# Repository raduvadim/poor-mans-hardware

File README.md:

poor-mans-hardware
==================

open source equipment for engineer's workbench.

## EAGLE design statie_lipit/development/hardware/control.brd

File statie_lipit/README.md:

Statie de lipit
=======================

Schema logica

+---------------+		+---------------+ 24Vcc	+---------------+	+---------------+
|		|     24Vca	|  Stabilizator	|======>|    Comanda	|	|     Letcon	|
|Transformator	| ============>	|  de tensiune	|	|   incalzire	|	+---------------+
|		|		|		|  /===>|		|==\	|    Element 	|
|---------------+		+---------------+  ||	+---------------+  \===>|   incalzire	|
					||	   ||				|		|
					||5Vcc	   ||				+---------------+
					\/	   ||				|     Senzor	|
+---------------+		+---------------+  ||	+---------------+   /===|  temperatura	|
|   Terminal	|      UART	| Microprocesor |===/	|   Convertor	|<==/	|		|
|    Serial	|==============>|    Atmega 8	| SPI/ V|  Temperatura	|	+---------------+
|		|		|		|<======| Tensiune/Biti |
+---------------+		+---------------+	+---------------+
				   ||	     /\	
				   ||	     ||
				   \/	     ||
			+---------------+    ||	+---------------+
			|     Afisaj    |    ||	|    Butoane/	|
			|  LCD/7segment |    \==|Encoder rotativ|
			| 		|	| /Potentiometru|
			+---------------+	+---------------+

Design modular
 -Circuitistica statiei de lipit este impartita in patru placi:
	-Alimentare si comanda incalzire
	-Microprocesor
	-Achizitie si conversie temperatura
	-Afisaj si input
 -Placile au dimensiunea de 2,4x1,5inch(6x3,8cm) si au 4 gauri de montare in colturi.

Model asezare placi:

	        +----------+     +     +     +     +
	       /	  /|====/|====/|====/|====/|
	      /		 / |   / |   / |   / |   / |
	     /		/  |  /	 |  /  |  /  |  /  |
	    /	       /   | /	 | /   | /   | /   |
	   /          /	   |/	 |/    |/    |/    | 
	  /	     /	   /	 /     /     /     +
	 /	    /	  /	/     /     /     /
	+----------+     +     +     +     +     /
	|	   |=====|=====|=====|=====|    /
	|	   |	/|    /|     |     |   /
	|   traf   |   / |   / |     |     |  /
	|	   |  /	 |  /  |     |     | /
	|	   |=====|=====|=====|=====|/ 
	+----------+     +     +     +     +
	
			 ^     ^     ^	   ^placa afisaj si butoane
			 |     |     placa microprocesor
		  	 |	placa achizitie temperatura	
			 placa stabilizare tensiune si control incalzire

Design frontal statie lipit:

	+----------------------------+
        |			     |
	| +---------------+	     |
	| |		  |   #####  |
	| |	LCD/	  |   #PWR#  |
	| |   7segmente	  |   #####  |
	| |		  |          |
	| +---------------+	     |
	|  /-\   /-\   /-\    #####  |
	|  \-/   \-/   \-/    #Con#  |
	|		      #####  |
        +----------------------------+

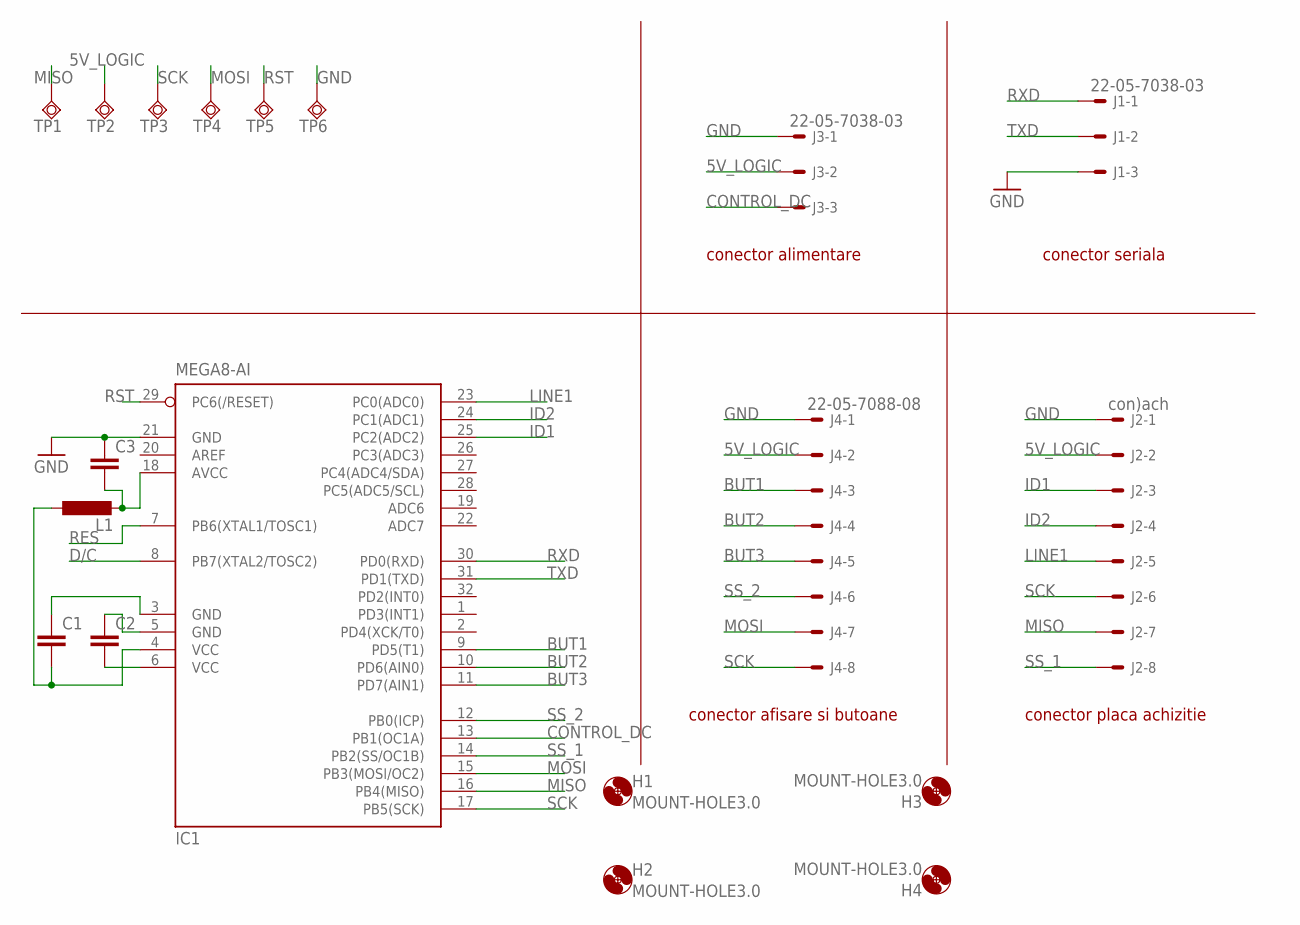
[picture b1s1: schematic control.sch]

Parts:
C1, C2, C3: C-EUC0805K; C0805K
H1, H2, H3, H4: MOUNT-HOLE3.0; 3,0
IC1: MEGA8-AI; TQFP32-08
J1, J3: 22-05-7038-03; 7395-03
J2: con)ach; 7395-08
J4: 22-05-7088-08; 7395-08
L1: L-EU0204/7; 0204/7
TP1, TP2, TP3, TP4, TP5, TP6: TPSQPAD1-13; P1-13

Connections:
5V_LOGIC: C1.2, C2.2, IC1.4 (VCC), IC1.6 (VCC), J2.2, J3.2, J4.2, L1.1, TP2.TP
BUT1: IC1.9 (PD5(T1)), J4.3
BUT2: IC1.10 (PD6(AIN0)), J4.4
BUT3: IC1.11 (PD7(AIN1)), J4.5
CONTROL_DC: IC1.13 (PB1(OC1A)), J3.3
D/C: IC1.8 (PB7(XTAL2/TOSC2))
GND: C1.1, C2.1, C3.1, IC1.3 (GND), IC1.5 (GND), IC1.21 (GND), J1.3, J2.1, J3.1, J4.1, TP6.TP
ID1: IC1.25 (PC2(ADC2)), J2.3
ID2: IC1.24 (PC1(ADC1)), J2.4
LINE1: IC1.23 (PC0(ADC0)), J2.5
MISO: IC1.16 (PB4(MISO)), J2.7, TP1.TP
MOSI: IC1.15 (PB3(MOSI/OC2)), J4.7, TP4.TP
unnamed: C3.2, IC1.18 (AVCC), L1.2
RES: IC1.7 (PB6(XTAL1/TOSC1))
RST: IC1.29 (PC6(/RESET)), TP5.TP
RXD: IC1.30 (PD0(RXD)), J1.1
SCK: IC1.17 (PB5(SCK)), J2.6, J4.8, TP3.TP
SS_1: IC1.14 (PB2(SS/OC1B)), J2.8
SS_2: IC1.12 (PB0(ICP)), J4.6
TXD: IC1.31 (PD1(TXD)), J1.2

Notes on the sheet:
conector seriala
conector placa achizitie
conector alimentare
conector afisare si butoane

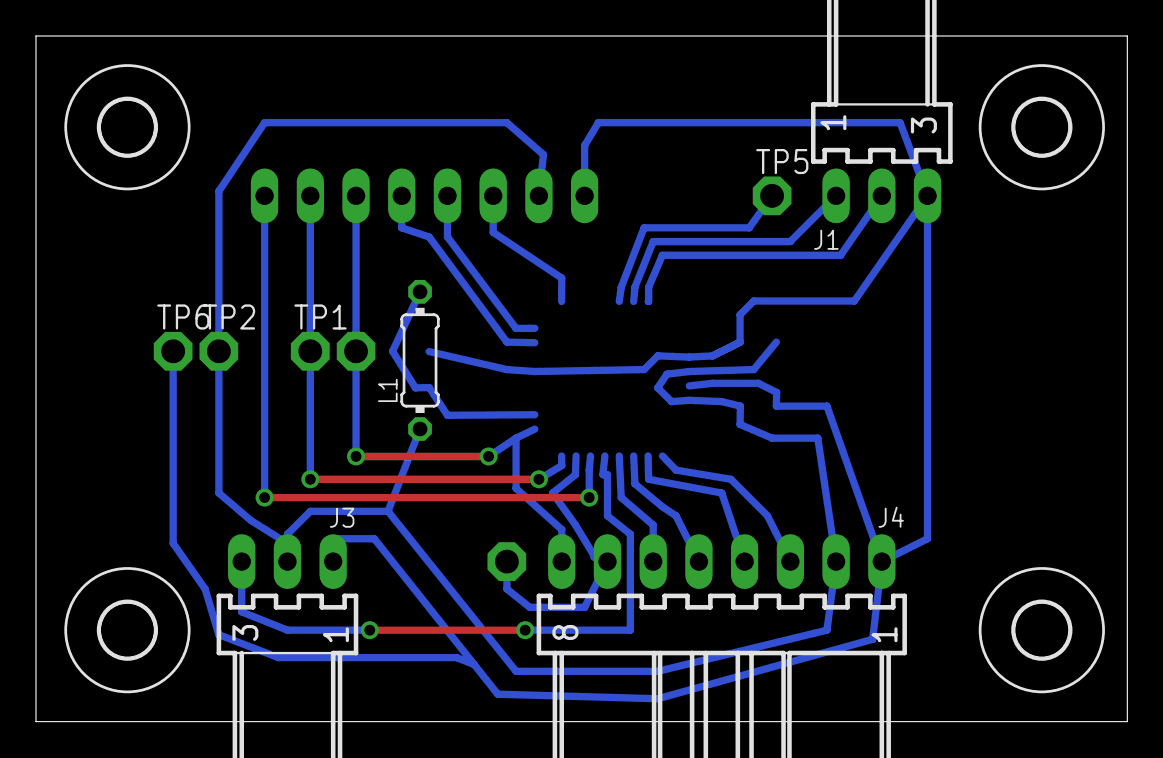
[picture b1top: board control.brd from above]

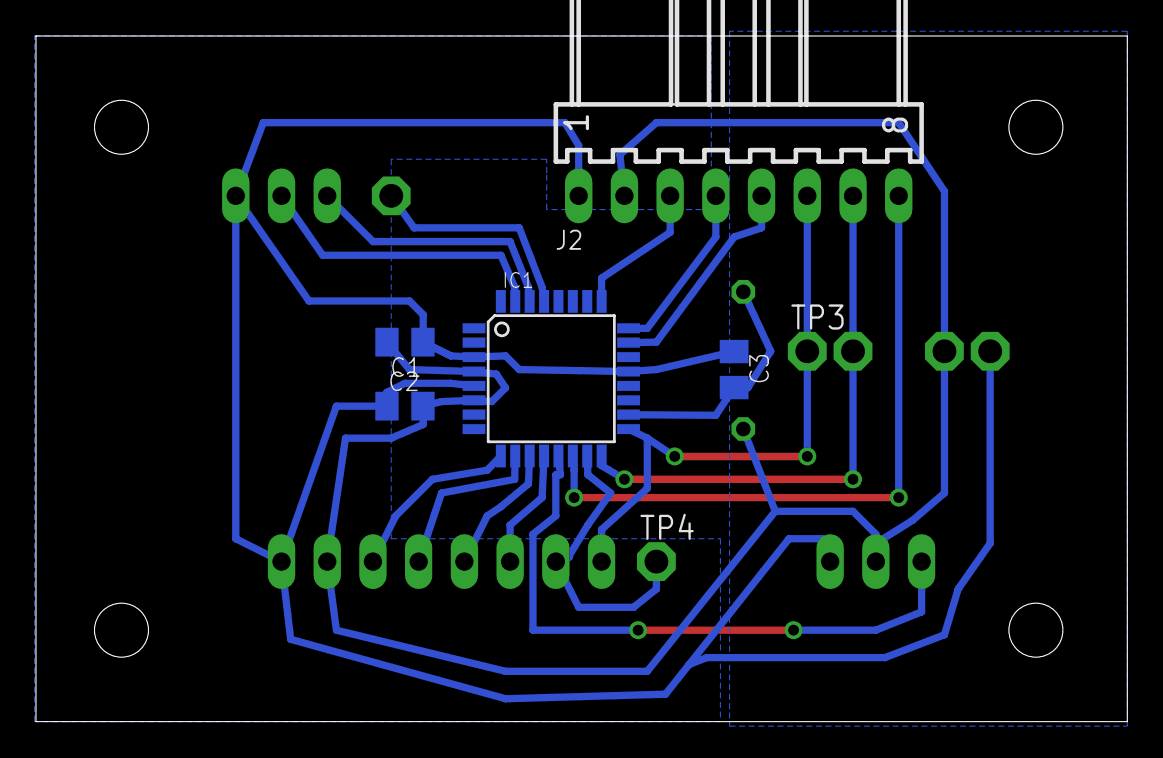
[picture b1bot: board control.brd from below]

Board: 2 copper layers, 60.6 x 38.1 mm, 19 parts (7 on the bottom side), 18 nets.

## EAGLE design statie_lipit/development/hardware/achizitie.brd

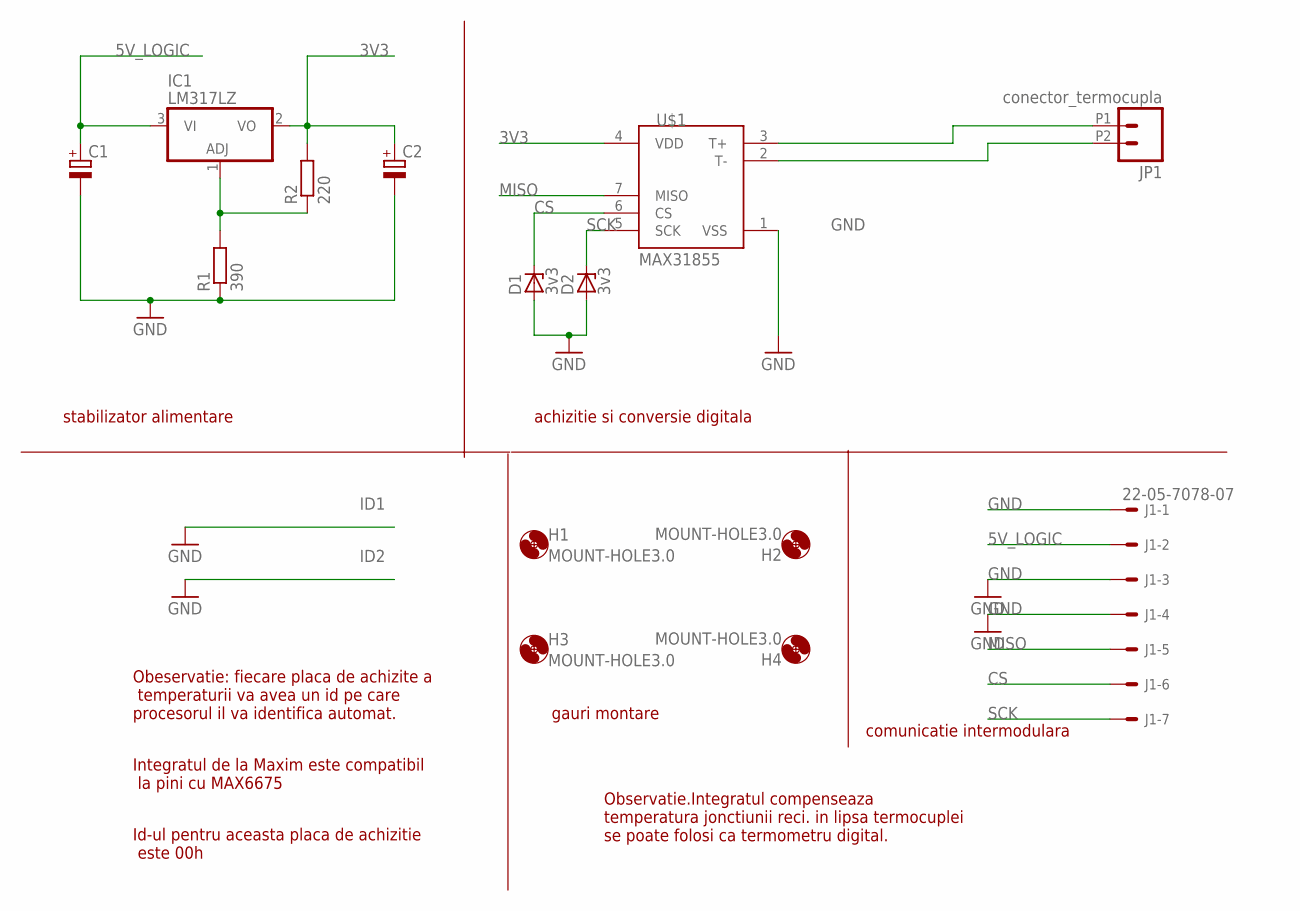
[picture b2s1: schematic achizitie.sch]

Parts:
C1, C2: CPOL-EUE2,5-6E; E2,5-6E
D1, D2: 3v3; SOD80C
H1, H2, H3, H4: MOUNT-HOLE3.0; 3,0
IC1: LM317LZ; TO92
J1: 22-05-7078-07; 7395-07
JP1: conector_termocupla; 1X02_2.54_SCREWTERM
R1: 390; M1206
R2: 220; M1206
U$1: MAX31855; SO08-MAX6675

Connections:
3V3: C2.+, IC1.2 (VO), R2.2, U$1.4 (VDD)
5V_LOGIC: C1.+, IC1.3 (VI), J1.2
CS: D1.C, J1.6, U$1.6 (CS)
GND: C1.-, C2.-, D1.A, D2.A, J1.1, J1.3, J1.4, R1.1, U$1.1 (VSS)
MISO: J1.5, U$1.7 (MISO)
unnamed: IC1.1 (ADJ), R1.2, R2.1
unnamed: JP1.P1 (1), U$1.3 (T+)
unnamed: JP1.P2 (2), U$1.2 (T-)
SCK: D2.C, J1.7, U$1.5 (SCK)

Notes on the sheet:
Obeservatie: fiecare placa de achizite a temperaturii va avea un id pe care procesorul il va identifica automat.
Integratul de la Maxim este compatibil la pini cu MAX6675
Id-ul pentru aceasta placa de achizitie este 00h
stabilizator alimentare
achizitie si conversie digitala
gauri montare
comunicatie intermodulara
Observatie.Integratul compenseaza temperatura jonctiunii reci. in lipsa termocuplei se poate folosi ca termometru digital.

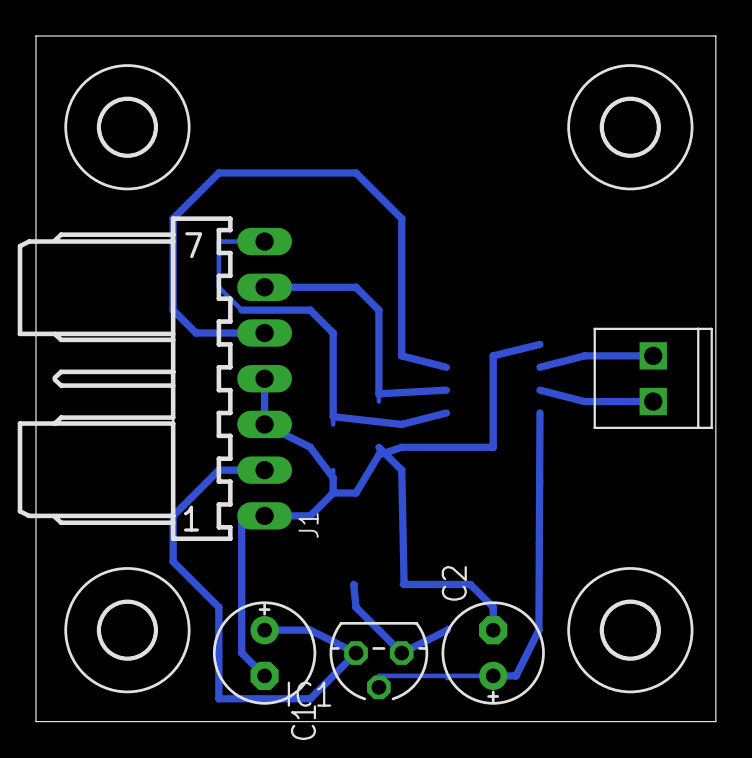
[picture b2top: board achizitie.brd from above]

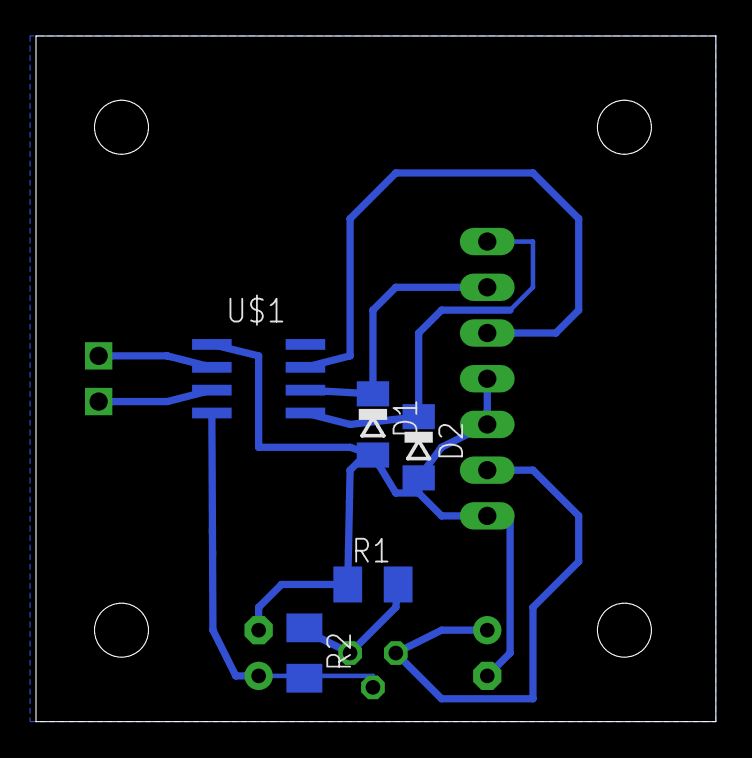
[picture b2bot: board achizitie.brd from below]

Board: 2 copper layers, 37.8 x 38.1 mm, 14 parts (5 on the bottom side), 9 nets.

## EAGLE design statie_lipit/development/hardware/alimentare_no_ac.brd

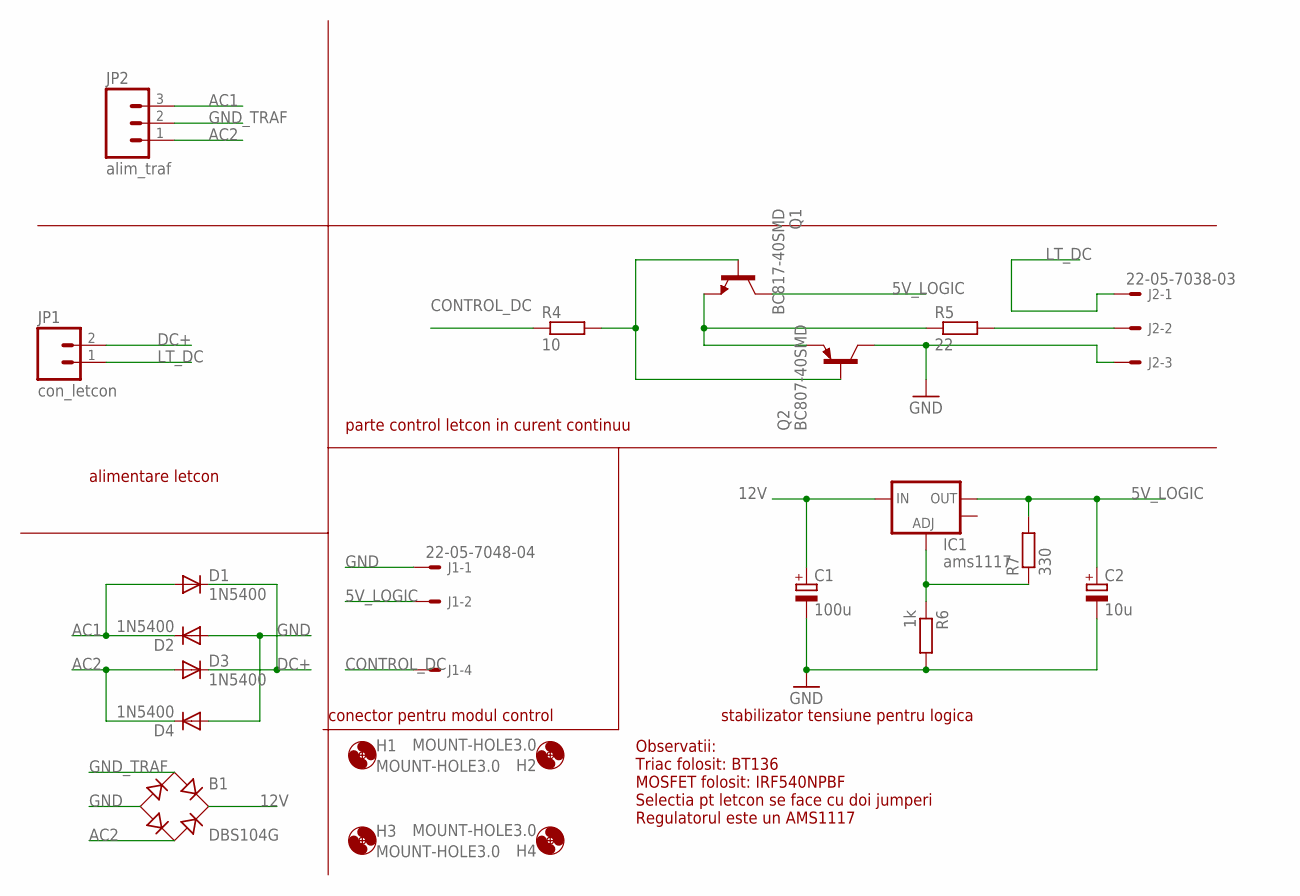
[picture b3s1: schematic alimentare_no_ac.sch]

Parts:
B1: DBS104G; DBS
C1: 100u; E2,5-6E
C2: 10u; E2,5-6E
D1, D2, D3, D4: 1N5400; DO201-15
H1, H2, H3, H4: MOUNT-HOLE3.0; 3,0
IC1: ams1117; SOT223
J1: 22-05-7048-04; 7395-04
J2: 22-05-7038-03; 7395-03
JP1: con_letcon; SCREWTERMINAL-3.5MM-2
JP2: alim_traf; SCREWTERMINAL-3.5MM-3
Q1: BC817-40SMD; SOT23-BEC
Q2: BC807-40SMD; SOT23-BEC
R4: 10; M1206
R5: 22; M1206
R6: 1k; M1206
R7: 330; M1206

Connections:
5V_LOGIC: C2.+, IC1.2 (OUT), J1.2, Q1.C, R7.2
12V: B1.+, C1.+, IC1.3 (IN)
AC1: D1.A, D2.C, JP2.3
AC2: B1.AC2, D3.A, D4.C, JP2.1
CONTROL_DC: J1.4, R4.1
DC+: D1.C, D3.C, JP1.2
GND: B1.-, C1.-, C2.-, D2.A, D4.A, J1.1, J2.3, Q2.C, R6.2
GND_TRAF: B1.AC1, JP2.2
LT_DC: J2.1, JP1.1
unnamed: J2.2, R5.2
unnamed: Q1.E, Q2.E, R5.1
unnamed: Q1.B, Q2.B, R4.2
unnamed: IC1.1 (ADJ), R6.1, R7.1

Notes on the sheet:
parte control letcon in curent continuu
stabilizator tensiune pentru logica
conector pentru modul control
Observatii: Triac folosit: BT136 MOSFET folosit: IRF540NPBF Selectia pt letcon se face cu doi jumperi Regulatorul este un AMS1117
alimentare letcon

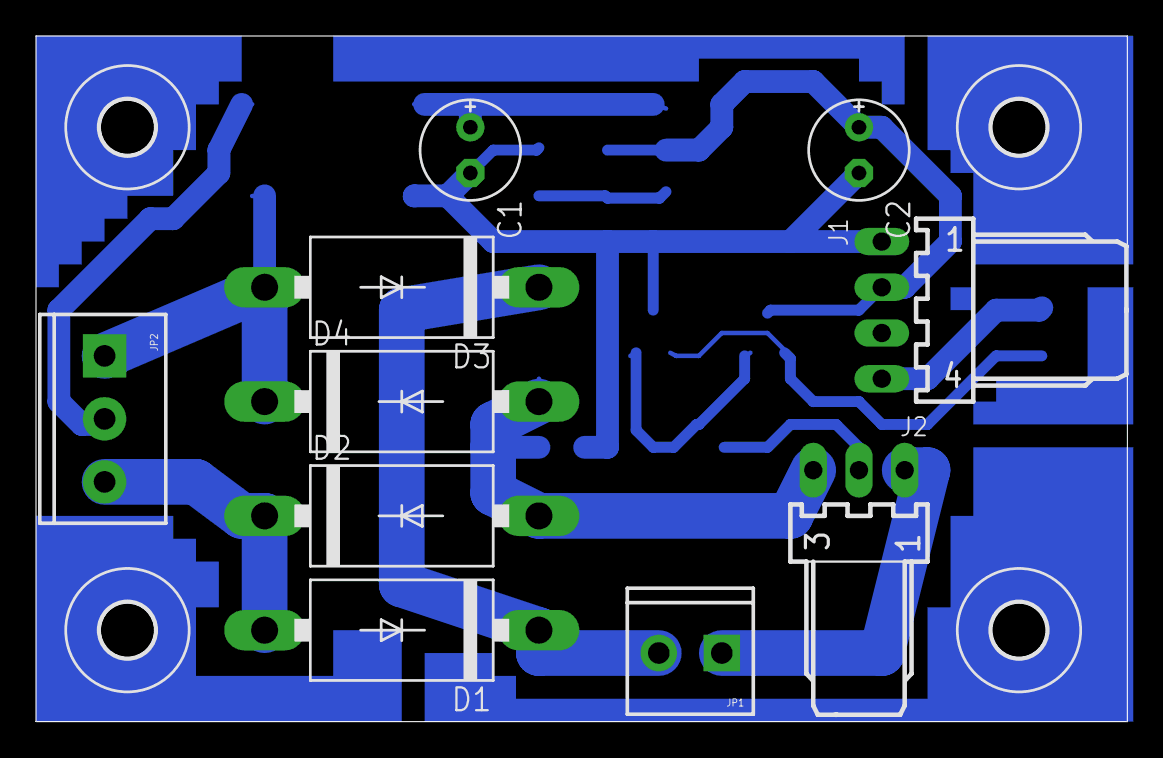
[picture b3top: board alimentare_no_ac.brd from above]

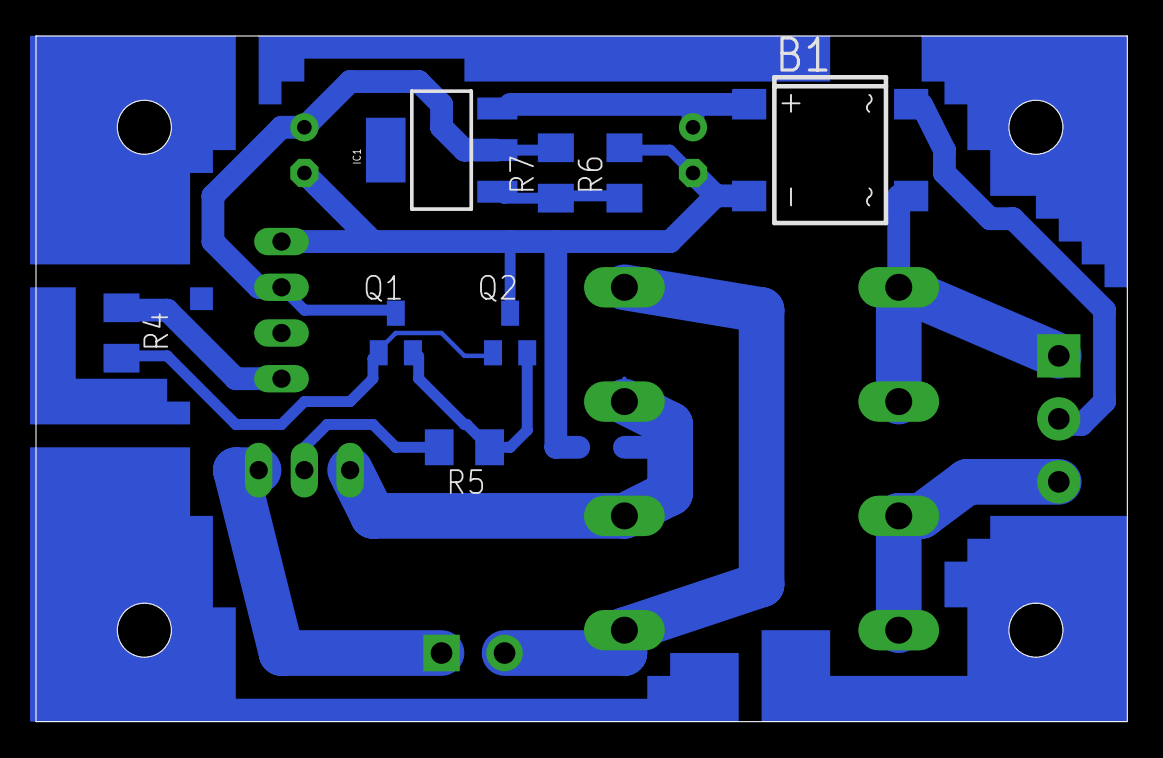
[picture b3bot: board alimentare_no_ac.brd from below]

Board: 2 copper layers, 60.6 x 38.1 mm, 22 parts (8 on the bottom side), 13 nets.

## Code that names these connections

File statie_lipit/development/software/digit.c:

/* Script afisare 7seg
 * 11/07/2014 vadim@home
 */
#include <avr/io.h>
#include <stdint.h>

#include "hardware.h"
//#include "spi.h"
#include "digit.h"

/* PB7 PB6 PB5 PB4 PB3 PB2 PB1 PB0
 *  A   B   C   D   E   F   G  DOT
 *   +----A----+
 *   |         |
 *   F         B
 *   |         |
 *   +----G----+
 *   |         |
 *   E         C
 *   |         |
 *   +----D----+  DOT
 * 
 * pinii sunt conectati pe considerente de catod comun
 */
//de modificat controlul in rev urmatoare
static uint8_t bcd_7seg[]= {0xFC, 0x60, 0xDC, 0xF2, 0x66, 0xB6, 0xBE, 0xE0, 0xFE, 0xF6};
void digit_print(uint8_t number){
	if(number > 9){
		DIGIT_PORT = 0x9E;
		return;
	}
	DIGIT_PORT = bcd_7seg[number];
} 
void digit_refresh(uint8_t nr1, uint8_t nr2, uint8_t nr3, uint8_t nr4){
	digit_print(nr1);
	//CATHODE_PORT=0; //primul segment 
	digit_print(nr2);
	//CATHODE_PORT=0; //primul segment 
	digit_print(nr3);
	//CATHODE_PORT=0; //primul segment 
	digit_print(nr4);
	//CATHODE_PORT=0; //primul segment 
}

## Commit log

2014-07-23 organizare structura
2014-07-23 primele versiuni de placa
2014-07-23 prima versiune de software
2014-07-23 targeturi software
2014-07-23 specificatie proiect
2014-07-23 minor adjustment
2014-07-26 revizie 1.1
    Au fost redefinite intreruperile.
    A fost adaugat controlul temperaturii pe interfata seriala.
2014-07-26 revizie 2.0
    oarecum limitata in functionalitate, se poate regla doar de pe portul
    serial.
2014-07-26 update todo list
2014-07-28 new hardware design

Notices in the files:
parts and their libraries:
SparkFun-AnalogIC: Licensing:Creative Commons ShareAlike 4.0 International - https://creativecommons.org/licenses/by-sa/4.0
